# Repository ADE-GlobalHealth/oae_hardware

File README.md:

# OAE Hardware

PCB designs for the OAE prototype.

+--------------------------------------------------------------------------------+
|UI: HARDWARE_AND_DESIGN_REPO/*This is a seperate structure to the firmwware schema*|
+--------------------------------------------------------------------------------+
| ├── README.md                                                                  |
| │   (Project explainer, context, future work, state, and usage instructions)   |
| ├── LICENSE                                                                    |
| │   (CERN-OHL-P License file)                                                  |
| ├── CONTRIBUTORS.md                                                            |
| │   (Rolling list of project contributors IP and not)                          |
| ├── oae_hardware/                                                              |
| │   ├── PCB_Files/                                                             |
| │   │   └── (Core Hardware PCB Files)                                          |
| │   └── Schematic_Layout/                                                      |
| │       └── (Core Hardware Schematic & Layout)                                 |
| ├── physical_device/                                                           |
| │   ├── Enclosure_3D_Models/                                                   |
| │   │   ├── Ear_Probe_CAD/                                                     |
| │   │   │   └── ear_probe.f3d (Ear probe CAD - Fusion)                         |
| │   │   ├── Shell_CAD/                                                         |
| │   │   │   └── shell.f3d (Shell CAD - Fusion)                                 |
| │   │   └── 3D_printing_files/                                                 |
| │   │       └── (e.g., STL files)                                              |
| │   ├── UI_PCB_Files/                                                          |
| │   │   └── (UI Schematic & Layout PCB files)                                  |
| │   └── BOM_Prototype.pdf (Bill of materials Per Unit BOM Prototype)           |
| └── design_assets/                                                             |
|     └── Front_Plate_Lasercut_Files/                                            |
|         ├── LED_Prototype/                                                     |
|         │   └── Faceplate.ai (Illustrator lasercut file)                       |
|         └── LCD_Prototype/                                                     |
|             ├── Faceplate.ai (Illustrator lasercut file)                       |
|             └── Faceplate_Illustrator/                                         |
|                 └── faceplate_files.ai (Additional Illustrator files)          |
+--------------------------------------------------------------------------------+

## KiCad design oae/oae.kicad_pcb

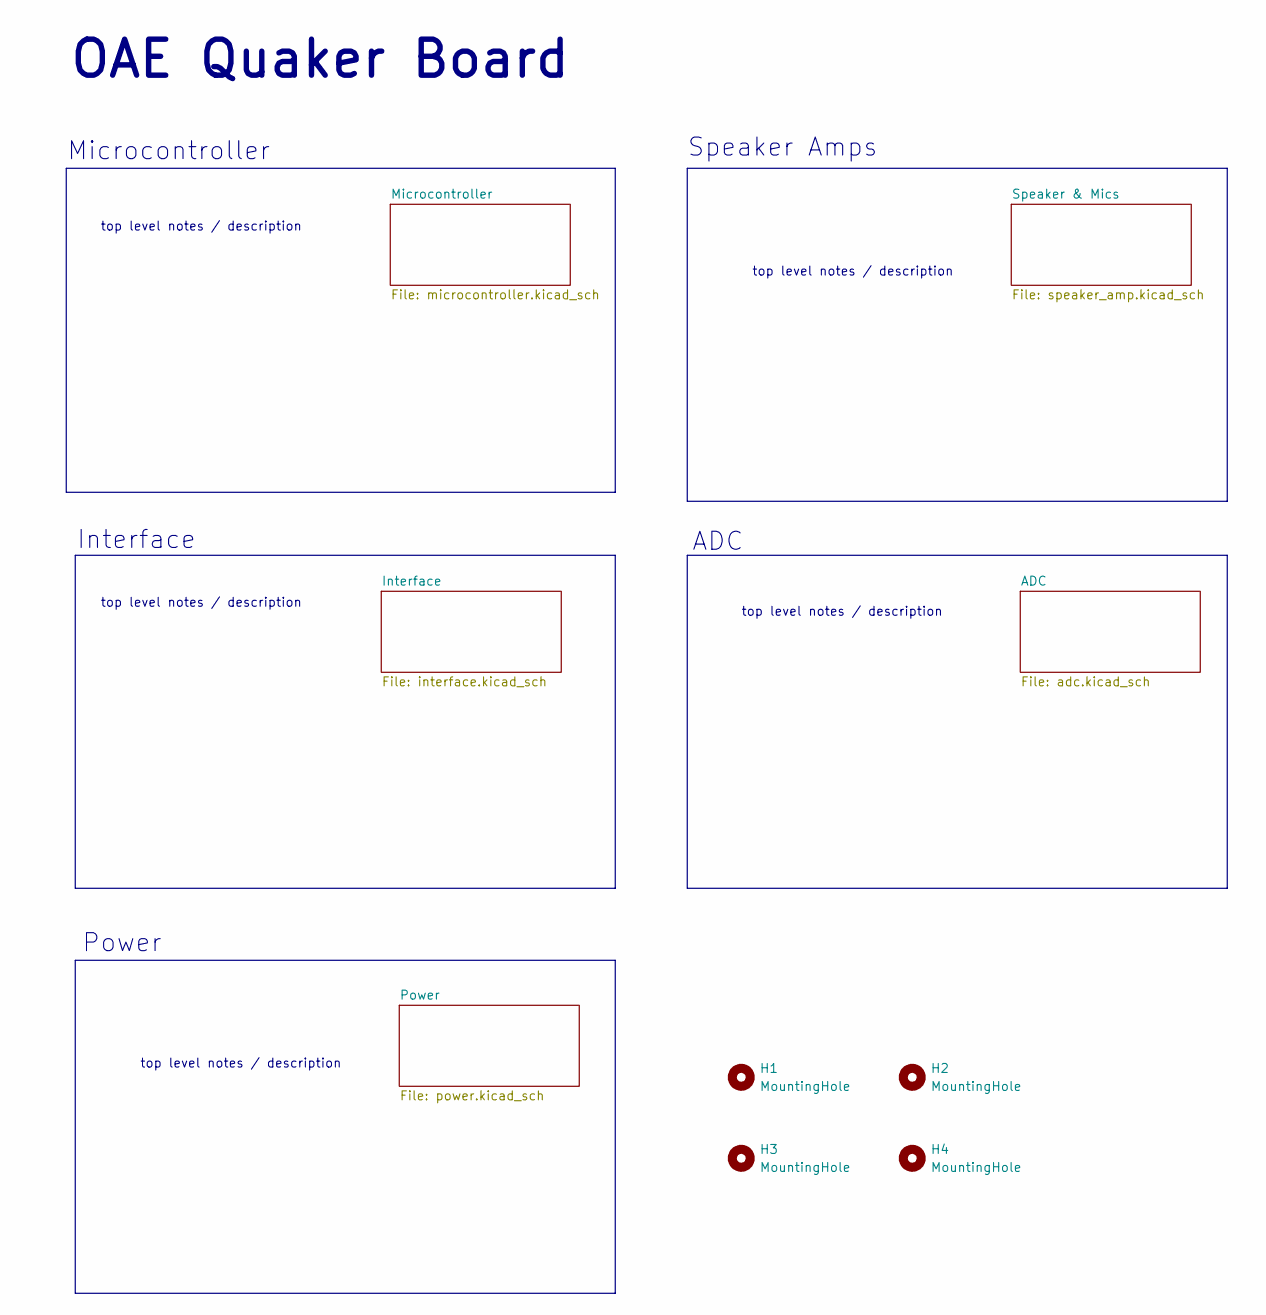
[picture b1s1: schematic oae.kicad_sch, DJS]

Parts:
H1, H2, H3, H4: MountingHole; MountingHole_2.7mm_Pad

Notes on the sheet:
Power
top level notes / description
Speaker Amps
Microcontroller
Interface
OAE Quaker Board
ADC

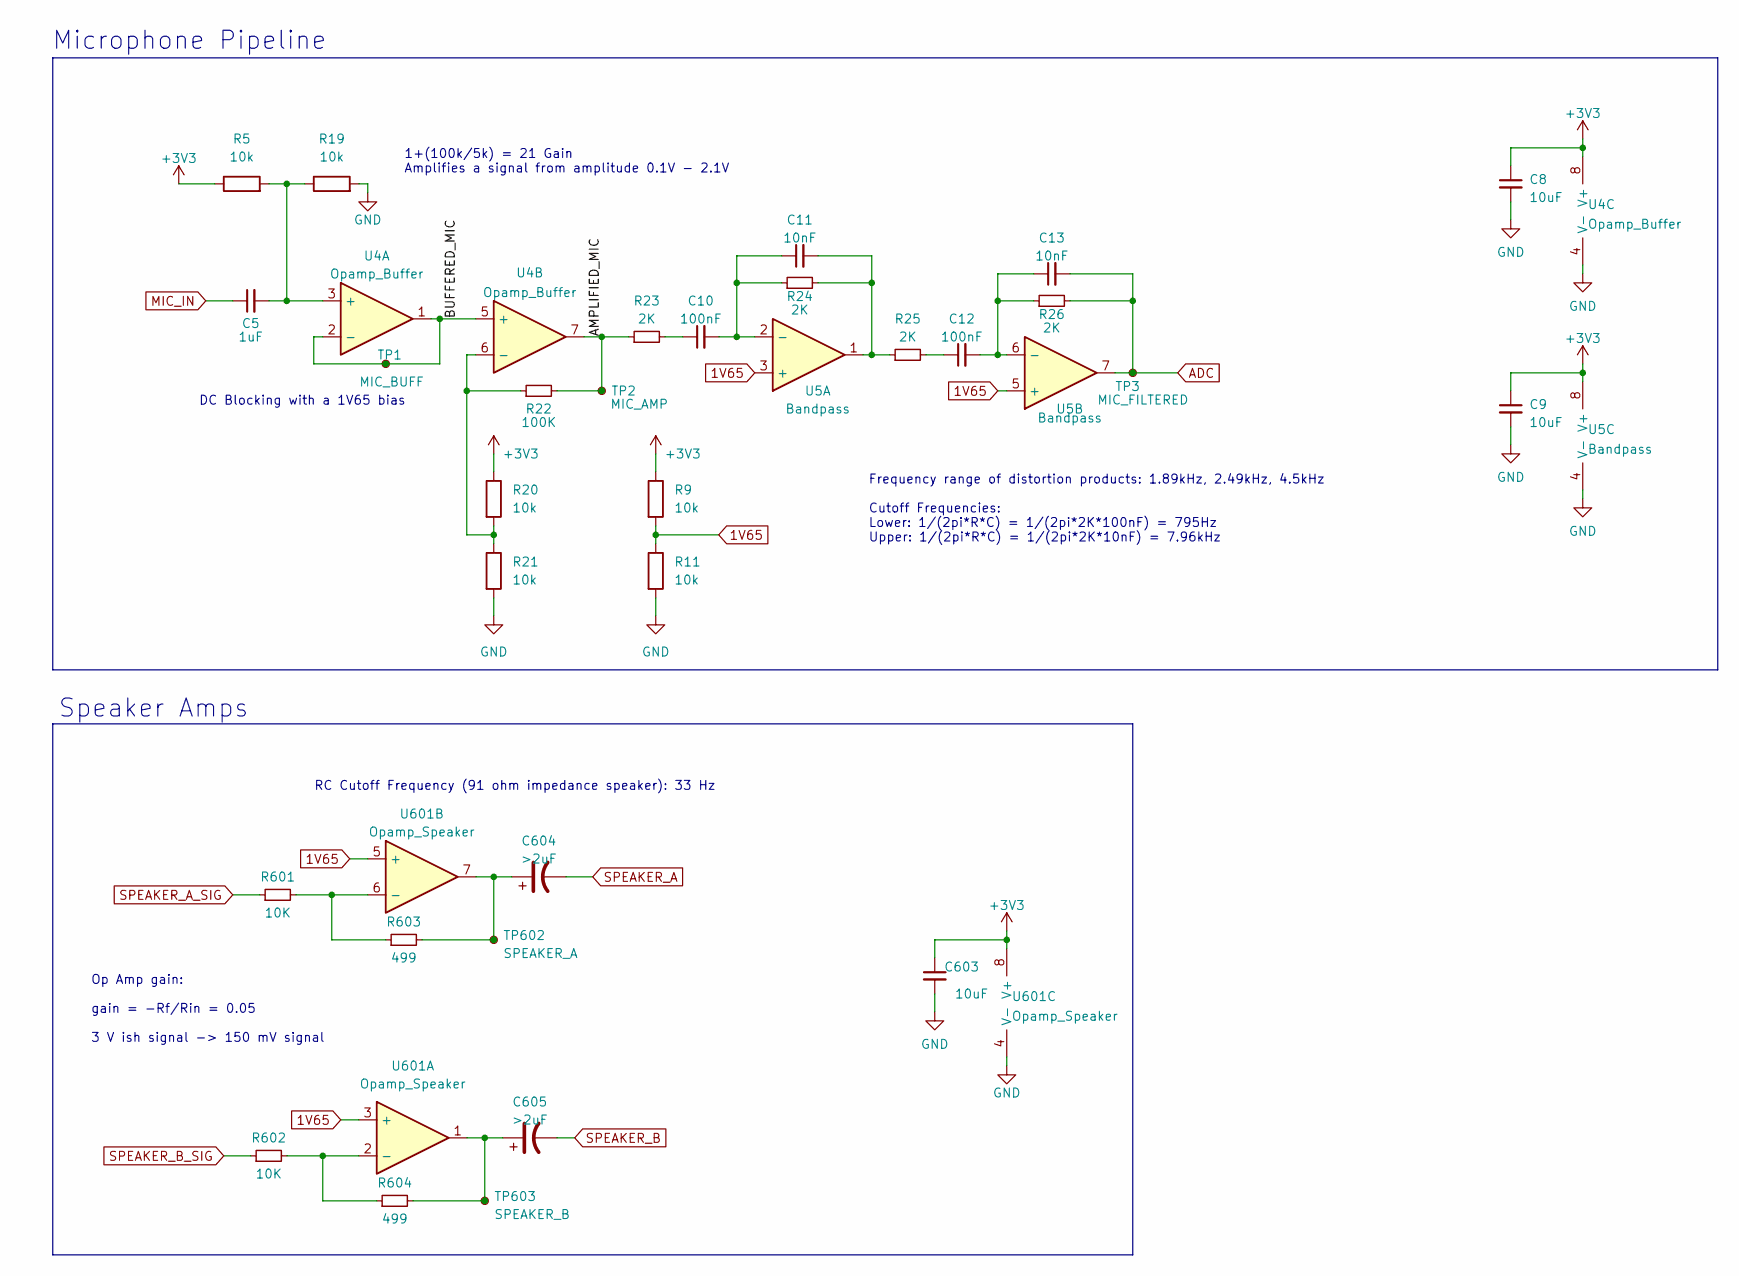
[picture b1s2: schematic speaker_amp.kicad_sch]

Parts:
C5: 1uF; C_1206_3216Metric_Pad1.33x1.80mm_HandSolder
C8, C9, C603: 10uF; C_0603_1608Metric
C10, C12: 100nF; C_1206_3216Metric
C11, C13: 10nF; C_0603_1608Metric
C604, C605: >2uF; C_0805_2012Metric_Pad1.18x1.45mm_HandSolder
R5, R9, R11, R19, R20, R21: 10k; R_0603_1608Metric
R22: 100K; R_0603_1608Metric_Pad0.98x0.95mm_HandSolder
R23, R24, R25, R26: 2K; R_0603_1608Metric_Pad0.98x0.95mm_HandSolder
R601, R602: 10K; R_0603_1608Metric_Pad0.98x0.95mm_HandSolder
R603, R604: 499; R_0603_1608Metric_Pad0.98x0.95mm_HandSolder
TP1: MIC_BUFF; TestPoint_Pad_D2.5mm
TP2: MIC_AMP; TestPoint_Pad_D2.5mm
TP3: MIC_FILTERED; TestPoint_Pad_D2.5mm
TP602: SPEAKER_A; TestPoint_Pad_D2.5mm
TP603: SPEAKER_B; TestPoint_Pad_D2.5mm
U2: PCM1862DBT; C_0603_1608Metric
U4: Opamp_Buffer; TSSOP-8_4.4x3mm_P0.65mm; Digikey MCP6022-I/SN-ND
U5: Bandpass; TSSOP-8_4.4x3mm_P0.65mm; Digikey MCP6022-I/SN-ND
U601: Opamp_Speaker; TSSOP-8_4.4x3mm_P0.65mm; Digikey MCP6022-I/SN-ND

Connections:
1V65: R9.2, R11.1, U5.3 (+), U5.5 (+), U601.3 (+), U601.5 (+)
+3V3: C8.1, C9.1, C603.1, R5.1, R9.1, R20.1, U4.8 (V+), U5.8 (V+), U601.8 (V+); also elsewhere on the board
/Speaker & Mics/AMPLIFIED_MIC: R22.2, R23.1, TP2.1 (1_1), U4.7
/Speaker & Mics/BUFFERED_MIC: TP1.1 (1_1), U4.1, U4.2 (-), U4.5 (+)
ADC: C13.2, R26.2, TP3.1 (1_1), U5.7; also elsewhere on the board
GND: C8.2, C9.2, C603.2, R11.2, R19.2, R21.2, U4.4 (V-), U5.4 (V-), U601.4 (V-); also elsewhere on the board
MIC_IN: C5.1; also elsewhere on the board
unnamed: C10.1, R23.2
unnamed: C11.2, R24.2, R25.1, U5.1
unnamed: C12.1, R25.2
unnamed: C604.1, R603.2, TP602.1 (1_1), U601.7
unnamed: C605.1, R604.2, TP603.1 (1_1), U601.1
unnamed: C5.2, R5.2, R19.1, U4.3 (+)
unnamed: R20.2, R21.1, R22.1, U4.6 (-)
unnamed: C10.2, C11.1, R24.1, U5.2 (-)
unnamed: C12.2, C13.1, R26.1, U5.6 (-)
unnamed: R602.2, R604.1, U601.2 (-)
unnamed: R601.2, R603.1, U601.6 (-)
SPEAKER_A: C604.2; also elsewhere on the board
SPEAKER_A_SIG: R601.1; also elsewhere on the board
SPEAKER_B: C605.2; also elsewhere on the board
SPEAKER_B_SIG: R602.1; also elsewhere on the board

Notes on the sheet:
1+(100k/5k) = 21 Gain Amplifies a signal from amplitude 0.1V - 2.1V
Speaker Amps
Frequency range of distortion products: 1.89kHz, 2.49kHz, 4.5kHz Cutoff Frequencies: Lower: 1/(2pi*R*C) = 1/(2pi*2K*100nF) = 795Hz Upper: 1/(2pi*R*C) = 1/(2pi*2K*10nF) = 7.96kHz
Op Amp gain: gain = -Rf/Rin = 0.05 3 V ish signal -> 150 mV signal
RC Cutoff Frequency (91 ohm impedance speaker): 33 Hz
DC Blocking with a 1V65 bias
Microphone Pipeline

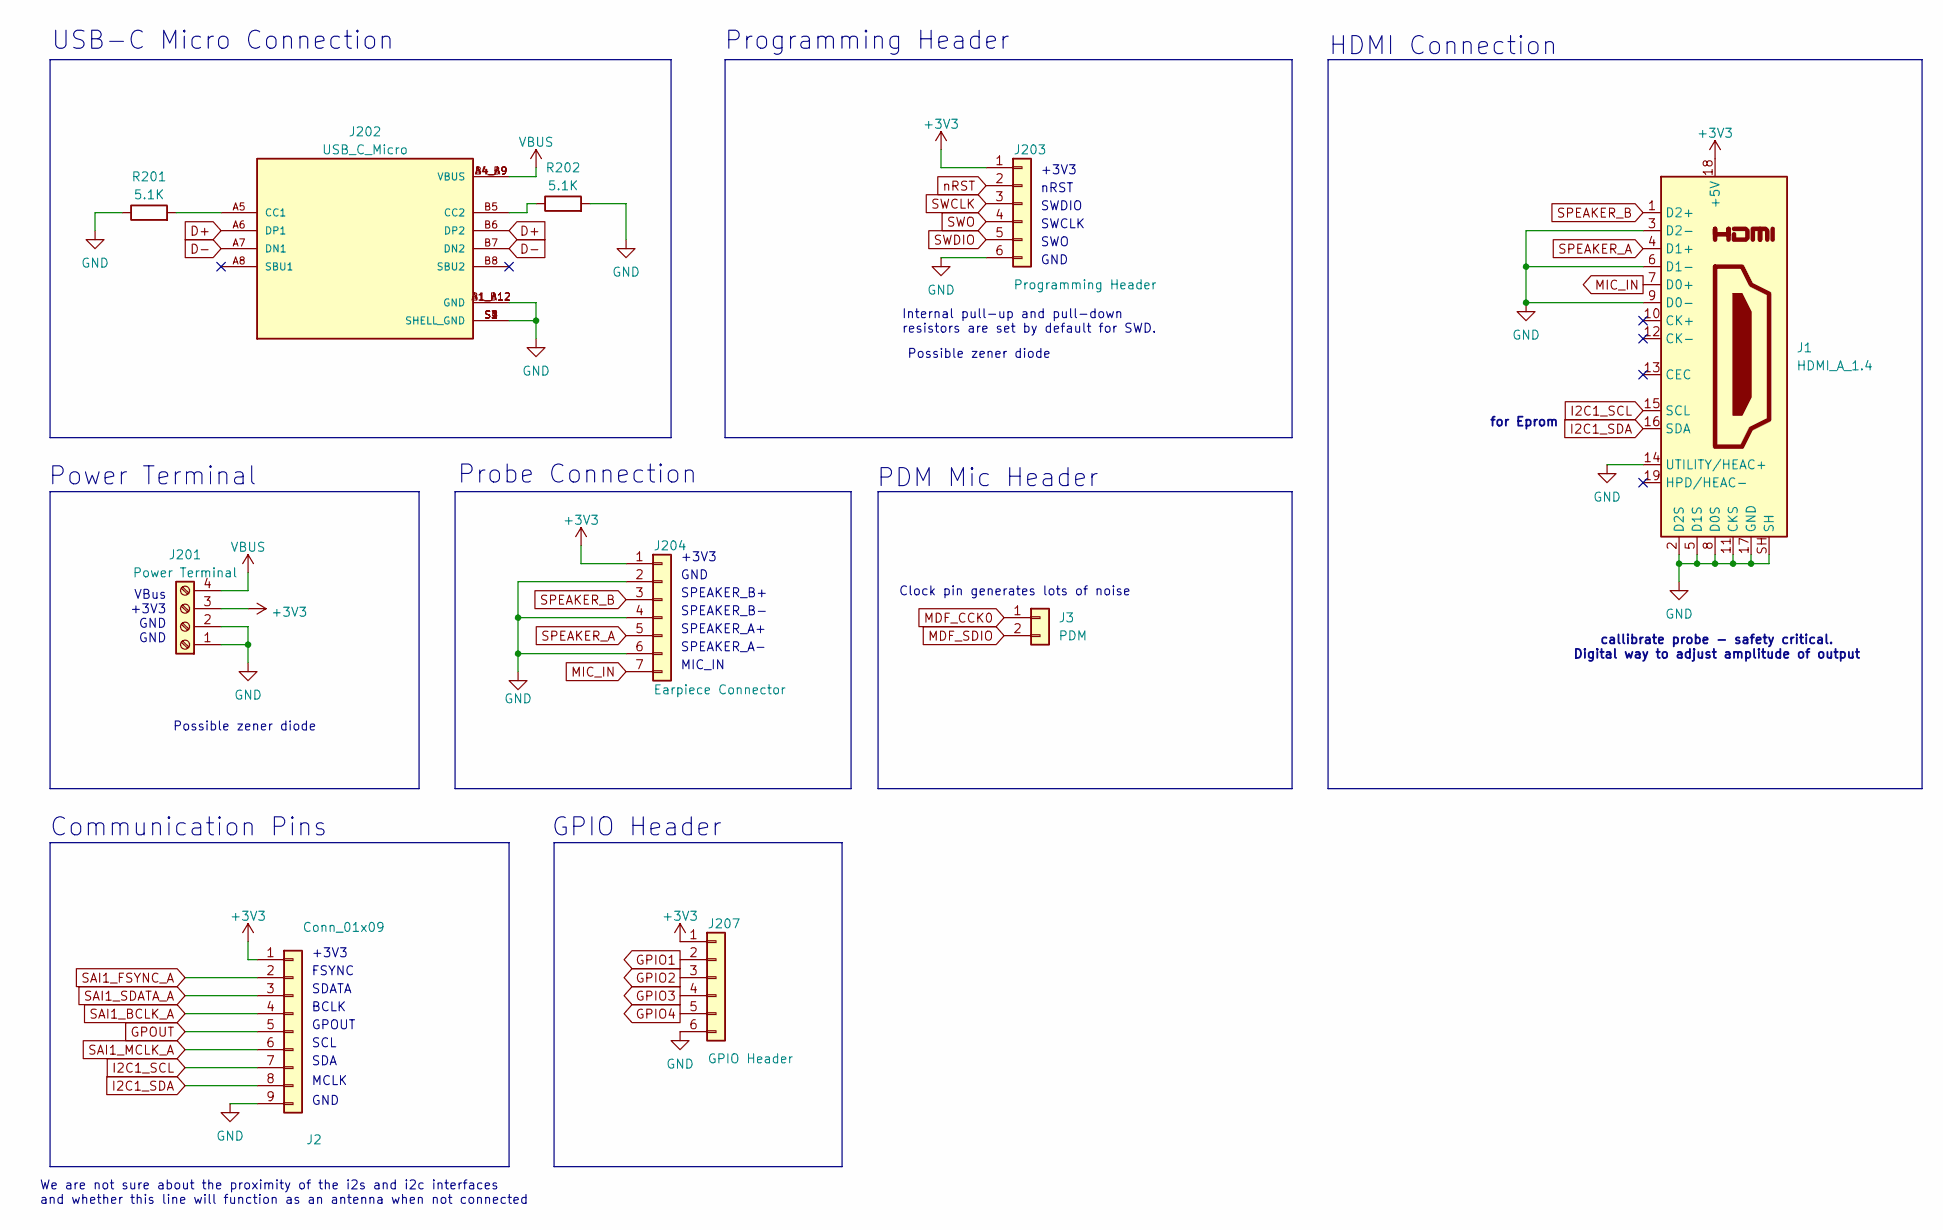
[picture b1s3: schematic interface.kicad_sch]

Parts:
J1: HDMI_A_1.4; HDMI_A_Molex_208658-1001_Horizontal
J2: Conn_01x09; PinHeader_1x09_P2.54mm_Vertical
J3: PDM; PinHeader_1x02_P2.54mm_Vertical
J201: Power Terminal; PinHeader_1x04_P2.54mm_Vertical
J202: USB_C_Micro; GCT_USB4105-GF-A; PARTREV A3
J203: Programming Header; PinHeader_1x06_P2.54mm_Vertical
J204: Earpiece Connector; PinHeader_1x07_P2.54mm_Vertical
J207: GPIO Header; PinHeader_1x06_P2.54mm_Vertical
R201, R202: 5.1K; R_0603_1608Metric_Pad0.98x0.95mm_HandSolder

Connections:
+3V3: J1.18 (+5V), J2.1, J201.3, J203.1, J204.1, J207.1; also elsewhere on the board
D+: J202.A6 (DP1), J202.B6 (DP2); also elsewhere on the board
D-: J202.A7 (DN1), J202.B7 (DN2); also elsewhere on the board
GND: J1.2 (D2S), J1.3 (D2-), J1.5 (D1S), J1.6 (D1-), J1.8 (D0S), J1.9 (D0-), J1.11 (CKS), J1.14 (UTILITY/HEAC+), J1.17 (GND), J1.SH, J2.9, J201.1, J201.2, J202.A1_B12 (GND), J202.B1_A12 (GND), J202.S1 (SHELL_GND), J202.S2 (SHELL_GND), J202.S3 (SHELL_GND), J202.S4 (SHELL_GND), J203.6, J204.2, J204.4, J204.6, J207.6, R201.1, R202.2; also elsewhere on the board
GPIO1: J207.2; also elsewhere on the board
GPIO2: J207.3; also elsewhere on the board
GPIO3: J207.4; also elsewhere on the board
GPIO4: J207.5; also elsewhere on the board
GPOUT: J2.5; also elsewhere on the board
I2C1_SCL: J1.15 (SCL), J2.7; also elsewhere on the board
I2C1_SDA: J1.16 (SDA), J2.8; also elsewhere on the board
MDF_CCK0: J3.1; also elsewhere on the board
MDF_SDIO: J3.2; also elsewhere on the board
MIC_IN: J1.7 (D0+), J204.7; also elsewhere on the board
unnamed: J202.A5 (CC1), R201.2
unnamed: J202.B5 (CC2), R202.1
SAI1_BCLK_A: J2.4; also elsewhere on the board
SAI1_FSYNC_A: J2.2; also elsewhere on the board
SAI1_MCLK_A: J2.6; also elsewhere on the board
SAI1_SDATA_A: J2.3; also elsewhere on the board
SPEAKER_A: J1.4 (D1+), J204.5; also elsewhere on the board
SPEAKER_B: J1.1 (D2+), J204.3; also elsewhere on the board
SWCLK: J203.3; also elsewhere on the board
SWDIO: J203.5; also elsewhere on the board
SWO: J203.4; also elsewhere on the board
VBUS: J201.4, J202.A4_B9 (VBUS), J202.B4_A9 (VBUS); also elsewhere on the board
nRST: J203.2; also elsewhere on the board

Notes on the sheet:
SPEAKER_B-
Communication Pins
SWO
MIC_IN
GPIO Header
VBus +3V3 GND GND
Clock pin generates lots of noise
BCLK
nRST
SPEAKER_A+
GND
FSYNC
Programming Header
SCL
Internal pull-up and pull-down resistors are set by default for SWD.
Probe Connection
+3V3
Possible zener diode
We are not sure about the proximity of the i2s and i2c interfaces and whether this line will function as an antenna when not connected
Power Terminal
SWCLK
MCLK
USB-C Micro Connection
SDA
SPEAKER_A-
SWDIO
SDATA
for Eprom
HDMI Connection
SPEAKER_B+
callibrate probe - safety critical. Digital way to adjust amplitude of output
GPOUT
PDM Mic Header

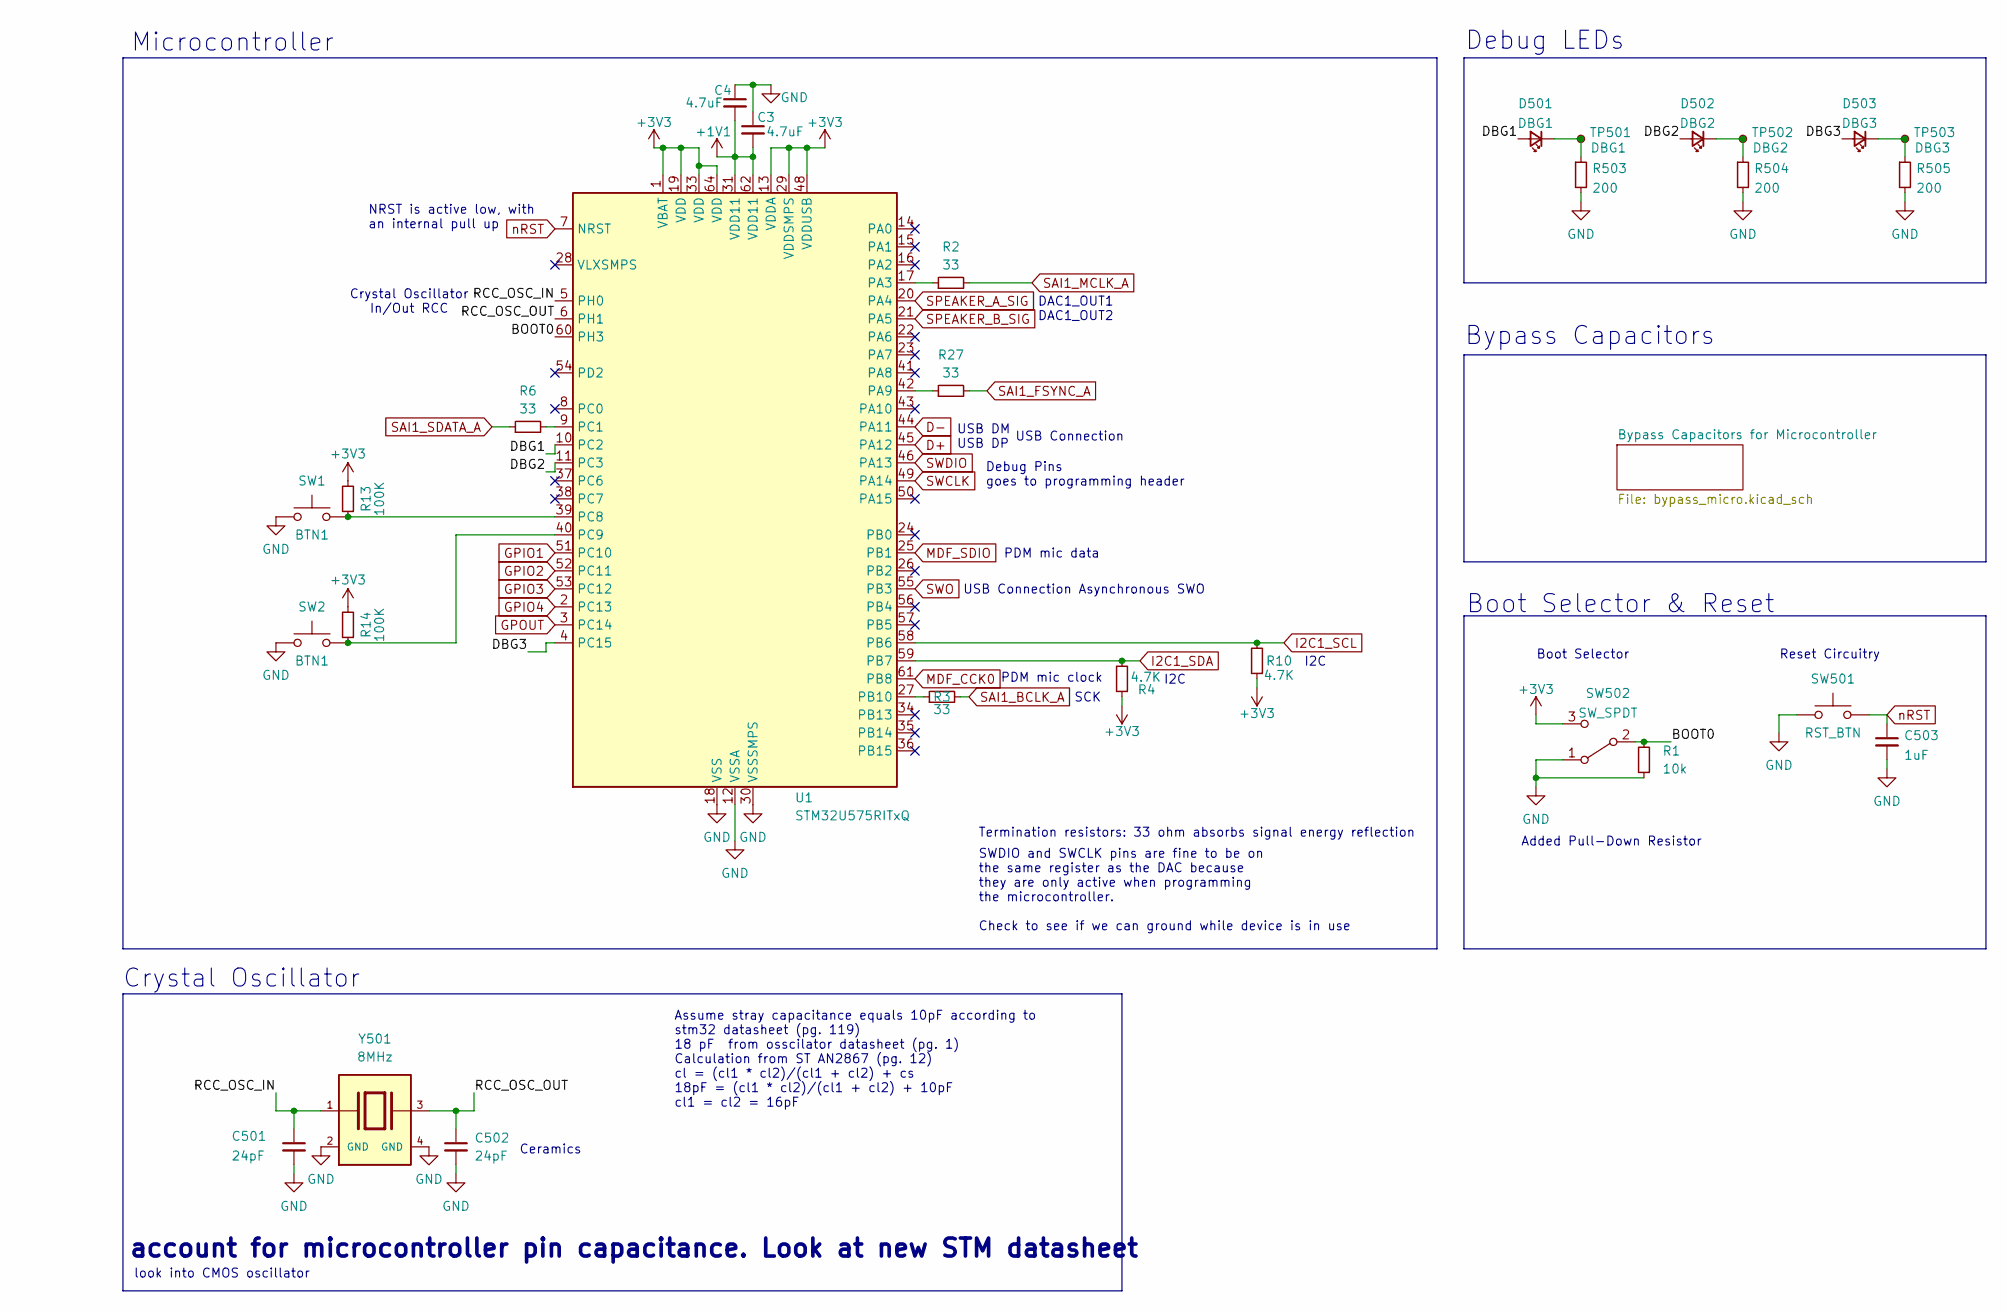
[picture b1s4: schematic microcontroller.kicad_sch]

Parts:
C3, C4: 4.7uF; C_0402_1005Metric
C501, C502: 24pF; C_0603_1608Metric
C503: 1uF; C_0603_1608Metric
D501: DBG1; LED_0603_1608Metric
D502: DBG2; LED_0603_1608Metric
D503: DBG3; LED_0603_1608Metric
R1: 10k; R_0603_1608Metric_Pad0.98x0.95mm_HandSolder
R2, R3, R6, R27: 33; R_0603_1608Metric_Pad0.98x0.95mm_HandSolder
R4, R10: 4.7K; R_0603_1608Metric_Pad0.98x0.95mm_HandSolder
R13, R14: 100K; R_0603_1608Metric_Pad0.98x0.95mm_HandSolder
R503, R504, R505: 200; R_0603_1608Metric_Pad0.98x0.95mm_HandSolder
SW1, SW2: BTN1; SW_SPST_EVPBF; DigiKey P19749DKR-ND
SW501: RST_BTN; SW_SPST_EVPBF; DigiKey P19749DKR-ND
SW502: SW_SPDT; PinHeader_1x03_P2.54mm_Vertical
TP501: DBG1; TestPoint_Pad_1.5x1.5mm
TP502: DBG2; TestPoint_Pad_1.5x1.5mm
TP503: DBG3; TestPoint_Pad_1.5x1.5mm
U1: STM32U575RITxQ; LQFP-64_10x10mm_P0.5mm
Y501: 8MHz; XTAL_ABMM2-8.000MHZ-E2-T; PARTREV 01.18.13

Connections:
+1V1: C3.2, C4.2, U1.31 (VDD11), U1.62 (VDD11)
+3V3: R4.1, R10.1, R13.2, R14.2, SW502.3 (C), U1.1 (VBAT), U1.13 (VDDA), U1.19 (VDD), U1.29 (VDDSMPS), U1.33 (VDD), U1.48 (VDDUSB), U1.64 (VDD); also elsewhere on the board
/Microcontroller/BOOT0: R1.2, SW502.2 (B), U1.60 (PH3)
/Microcontroller/DBG1: D501.2 (A), U1.10 (PC2)
/Microcontroller/DBG2: D502.2 (A), U1.11 (PC3)
/Microcontroller/DBG3: D503.2 (A), U1.4 (PC15)
/Microcontroller/RCC_OSC_IN: C501.1, U1.5 (PH0), Y501.1
/Microcontroller/RCC_OSC_OUT: C502.1, U1.6 (PH1), Y501.3
D+: U1.45 (PA12); also elsewhere on the board
D-: U1.44 (PA11); also elsewhere on the board
GND: C3.1, C4.1, C501.2, C502.2, C503.2, R1.1, R503.2, R504.2, R505.2, SW1.1, SW2.1, SW501.1, SW502.1 (A), U1.12 (VSSA), U1.18 (VSS), U1.30 (VSSSMPS), U1.32 (VSS), U1.47 (VSS), U1.63 (VSS), Y501.2 (GND), Y501.4 (GND); also elsewhere on the board
GPIO1: U1.51 (PC10); also elsewhere on the board
GPIO2: U1.52 (PC11); also elsewhere on the board
GPIO3: U1.53 (PC12); also elsewhere on the board
GPIO4: U1.2 (PC13); also elsewhere on the board
GPOUT: U1.3 (PC14); also elsewhere on the board
I2C1_SCL: R10.2, U1.58 (PB6); also elsewhere on the board
I2C1_SDA: R4.2, U1.59 (PB7); also elsewhere on the board
MDF_CCK0: U1.61 (PB8); also elsewhere on the board
MDF_SDIO: U1.25 (PB1); also elsewhere on the board
unnamed: D501.1 (K), R503.1, TP501.1 (1_1)
unnamed: D502.1 (K), R504.1, TP502.1 (1_1)
unnamed: D503.1 (K), R505.1, TP503.1 (1_1)
unnamed: R2.1, U1.17 (PA3)
unnamed: R27.1, U1.42 (PA9)
unnamed: R3.1, U1.27 (PB10)
unnamed: R6.2, U1.9 (PC1)
unnamed: R13.1, SW1.2, U1.39 (PC8)
unnamed: R14.1, SW2.2, U1.40 (PC9)
SAI1_BCLK_A: R3.2; also elsewhere on the board
SAI1_FSYNC_A: R27.2; also elsewhere on the board
SAI1_MCLK_A: R2.2; also elsewhere on the board
SAI1_SDATA_A: R6.1; also elsewhere on the board
SPEAKER_A_SIG: U1.20 (PA4); also elsewhere on the board
SPEAKER_B_SIG: U1.21 (PA5); also elsewhere on the board
SWCLK: U1.49 (PA14); also elsewhere on the board
SWDIO: U1.46 (PA13); also elsewhere on the board
SWO: U1.55 (PB3); also elsewhere on the board
nRST: C503.1, SW501.2, U1.7 (NRST); also elsewhere on the board

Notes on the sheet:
Ceramics
USB DM USB DP
PDM mic data
Bypass Capacitors
Crystal Oscillator
SCK
Boot Selector & Reset
Reset Circuitry
Termination resistors: 33 ohm absorbs signal energy reflection
USB Connection
Microcontroller
Boot Selector
I2C
account for microcontroller pin capacitance. Look at new STM datasheet
Debug LEDs
Assume stray capacitance equals 10pF according to stm32 datasheet (pg. 119) 18 pF from osscilator datasheet (pg. 1) Calculation from ST AN2867 (pg. 12) cl = (cl1 * cl2)/(cl1 + cl2) + cs 18pF = (cl1 * cl2)/(cl1 + cl2) + 10pF cl1 = cl2 = 16pF
NRST is active low, with an internal pull up
USB Connection Asynchronous SWO
Debug Pins goes to programming header
Crystal Oscillator In/Out RCC
SWDIO and SWCLK pins are fine to be on the same register as the DAC because they are only active when programming the microcontroller. Check to see if we can ground while device is in use
PDM mic clock
look into CMOS oscillator
Added Pull-Down Resistor
DAC1_OUT1 DAC1_OUT2

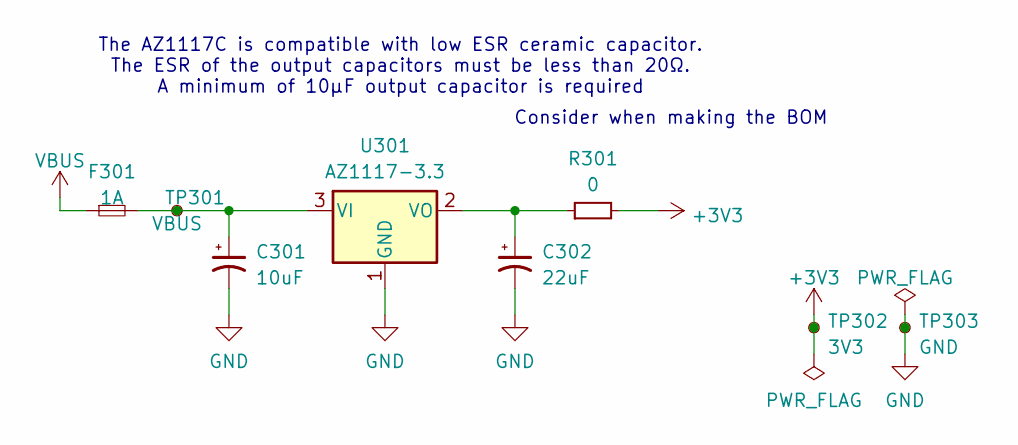
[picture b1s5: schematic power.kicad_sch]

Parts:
C301: 10uF; C_0603_1608Metric
C302: 22uF; C_0603_1608Metric
F301: 1A; Fuse_1206_3216Metric; DigiKey 507-1806-6-ND
R301: 0; R_0603_1608Metric_Pad0.98x0.95mm_HandSolder
TP301: VBUS; TestPoint_Pad_D2.5mm
TP302: 3V3; TestPoint_Pad_D2.5mm
TP303: GND; TestPoint_Pad_D2.5mm
U301: AZ1117-3.3; TO-252-3_TabPin2; DigiKey AZ1117CD-3.3TRG1DIDKR-ND

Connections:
+3V3: R301.2, TP302.1 (1_1); also elsewhere on the board
GND: C301.2, C302.2, TP303.1 (1_1), U301.1 (GND); also elsewhere on the board
unnamed: C301.1, F301.2, TP301.1 (1_1), U301.3 (VI)
unnamed: C302.1, R301.1, U301.2 (VO)
VBUS: F301.1; also elsewhere on the board

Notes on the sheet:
Consider when making the BOM
The AZ1117C is compatible with low ESR ceramic capacitor. The ESR of the output capacitors must be less than 20Ω. A minimum of 10µF output capacitor is required

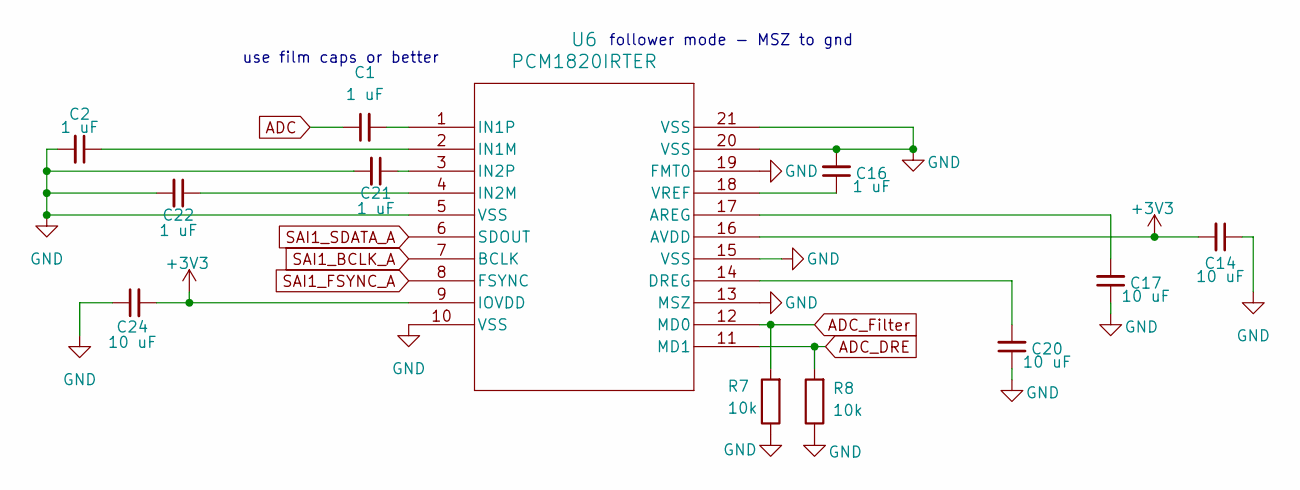
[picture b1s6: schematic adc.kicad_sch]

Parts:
C1, C2, C16, C21, C22: 1 uF; C_0603_1608Metric
C14, C17, C20, C24: 10 uF; C_0603_1608Metric
R7, R8: 10k; R_0603_1608Metric
U6: PCM1820IRTER; QFN_820IRTER_TEX

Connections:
+3V3: C14.2, C24.2, U6.9 (IOVDD), U6.16 (AVDD); also elsewhere on the board
ADC: C1.1; also elsewhere on the board
ADC_DRE: R8.2, U6.11 (MD1)
ADC_Filter: R7.2, U6.12 (MD0)
GND: C2.2, C14.1, C16.2, C17.1, C20.1, C21.2, C22.2, C24.1, R7.1, R8.1, U6.5 (VSS), U6.10 (VSS), U6.13 (MSZ), U6.15 (VSS), U6.19 (FMT0), U6.20 (VSS), U6.21 (VSS); also elsewhere on the board
unnamed: C17.2, U6.17 (AREG)
unnamed: C20.2, U6.14 (DREG)
unnamed: C2.1, U6.2 (IN1M)
unnamed: C1.2, U6.1 (IN1P)
unnamed: C22.1, U6.4 (IN2M)
unnamed: C21.1, U6.3 (IN2P)
unnamed: C16.1, U6.18 (VREF)
SAI1_BCLK_A: U6.7 (BCLK); also elsewhere on the board
SAI1_FSYNC_A: U6.8 (FSYNC); also elsewhere on the board
SAI1_SDATA_A: U6.6 (SDOUT); also elsewhere on the board

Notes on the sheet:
follower mode - MSZ to gnd
use film caps or better

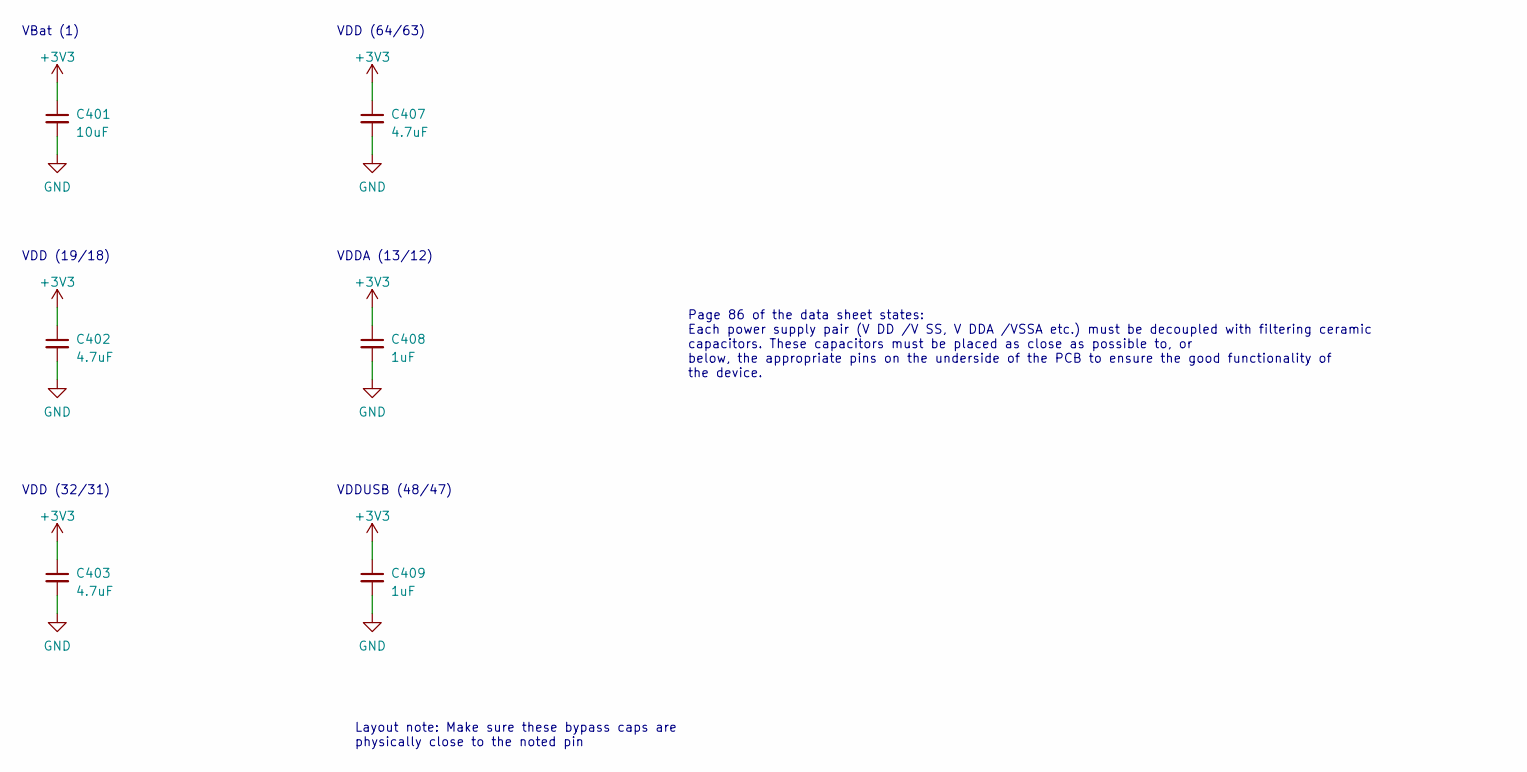
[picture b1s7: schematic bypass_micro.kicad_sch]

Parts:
C401: 10uF; C_0603_1608Metric
C402, C403, C407: 4.7uF; C_0603_1608Metric
C408, C409: 1uF; C_0603_1608Metric

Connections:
+3V3: C401.1, C402.1, C403.1, C407.1, C408.1, C409.1; also elsewhere on the board
GND: C401.2, C402.2, C403.2, C407.2, C408.2, C409.2; also elsewhere on the board

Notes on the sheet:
VBat (1)
VDD (64/63)
Layout note: Make sure these bypass caps are physically close to the noted pin
VDD (32/31)
VDD (19/18)
VDDA (13/12)
Page 86 of the data sheet states: Each power supply pair (V DD /V SS, V DDA /VSSA etc.) must be decoupled with filtering ceramic capacitors. These capacitors must be placed as close as possible to, or below, the appropriate pins on the underside of the PCB to ensure the good functionality of the de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
VDDUSB (48/47)

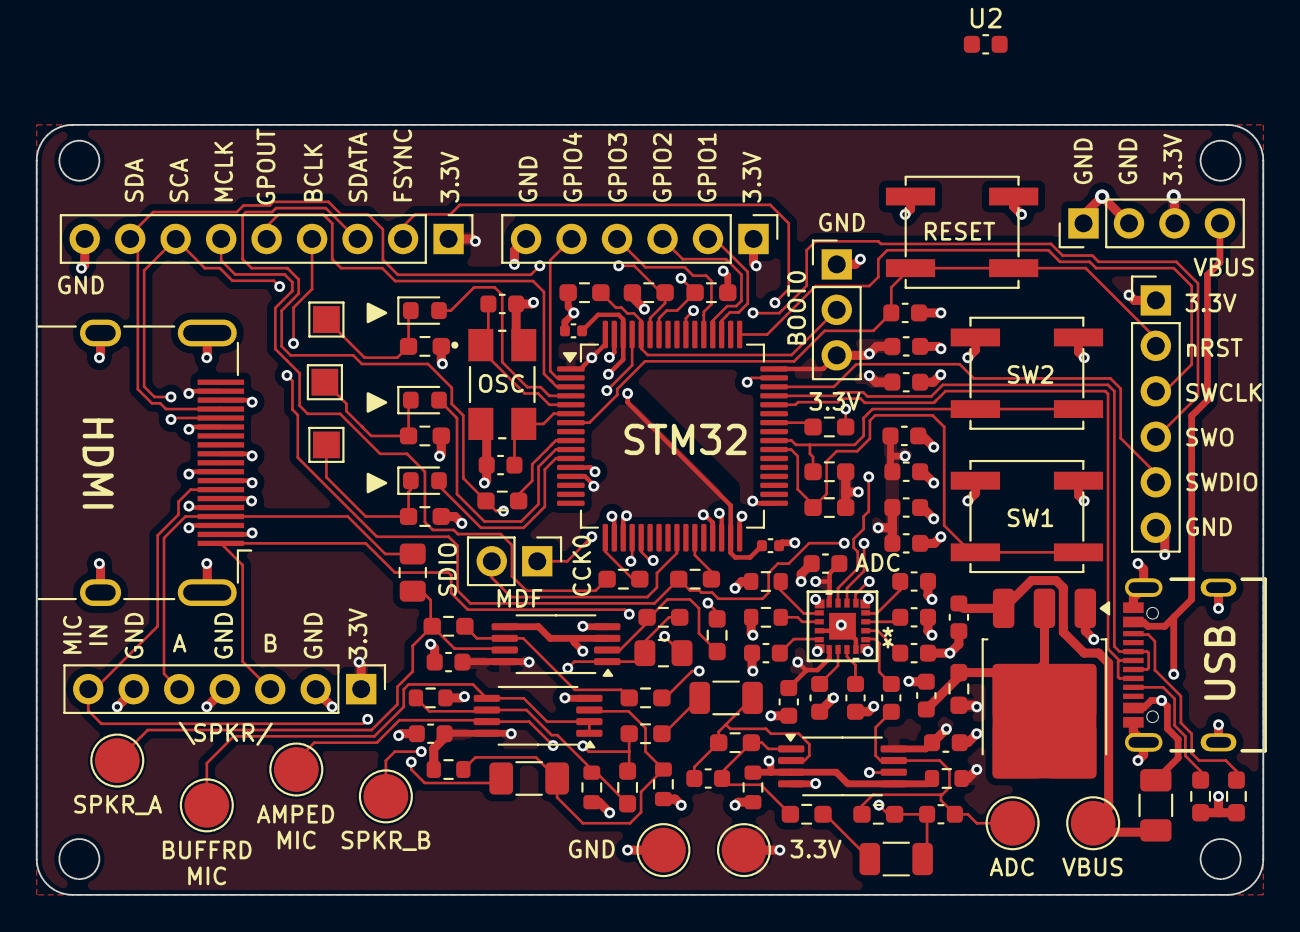
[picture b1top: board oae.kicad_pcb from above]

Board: 4 copper layers, 68.5 x 43.0 mm, 99 parts (0 on the bottom side), 71 nets.

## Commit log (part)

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2023-06-28 Removed schematic short; Added LTSpice schmatic for circuit validation
2023-06-29 Adjusted signal chain amplification issue in schematic
2023-06-29 Rearranged buffer/amplifier components on PCB (See comment)
2023-06-30 Changed LME49723 to MCP6001 RtR
2023-06-30 Moved voltage divider to non-inverting input
2023-07-03 Add ADC communication lines
2023-07-03 Changed resistor footprints
2023-07-03 Redefined ref voltage; Changed USB socket footprint; Added data lines; Altered Crystal Resonator
2023-07-05 Add ADC + power wiring into schematic
2023-07-05 Altered crystal footprint; Switched to USB-C; MCP6022-i/sn in use
2023-07-05 Fixed VBUS routing
2023-07-05 Routed USB-C Power
2023-07-05 Add jumpers for ADC GPIO pins
2023-07-05 Condensed board layout
2023-07-05 Routed ADC to MSC
2023-07-06 Add bypass capacitors
2023-07-06 Add resistors to power supply
2023-07-06 Reconfigure microcontroller pins
    - Remove SPI
    - Remove USART
    - Remove ADC mic input
    - Add I2C
    - Add I2S
    - Add USB
2023-07-06 Change ADC footprint
2023-07-06 Update interfaces to match pins
2023-07-06 Add extra bypass capacitor
2023-07-06 Changed Reference Voltage
2023-07-07 Initial review
2023-07-07 Review from Brad
2026-01-03 Update README with project structure and file details
    Expanded the README to include a detailed project structure with file descriptions.
